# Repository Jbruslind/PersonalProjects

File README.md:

#	Personal projects

This section contains all the personal projects I'm currently working on or have worked on/finished 
(who am I kidding they're never finished). Each directory should have it's own README with details about 
what the project is and the steps I took to do it. Some of my personal favorites are: 

##	Infinity Stone Pendants 
This project was inspired by Marvel's blockbuster hits (Avengers and their derivatives) and because of a 
gift I had made previously for an old high school friend. There isn't any functional point to this, mostly
just for sentimental value.

The design revolves around the use of [Tritium](https://nuclearsafety.gc.ca/eng/pdfs/Fact_Sheets/January-2013-Fact-Sheet-Tritium_e.pdf) 
which is a radioactive isotope of hydrogen. It's not radioactive in the sense that it'll cause damage, 
just enough to create some cool glowing effects. The radiation is low levels of Beta-particles and is not
damaging unless ingested (so just don't eat the vials). Using this as a core, I created geometric designs 
corresponding to each stone and their back story/ability. 

Here's a picture of the full assembly. The metal colors are pretty off due to Inventor having weird colors...

## More information can be found [here!](https://github.com/Jbruslind/PersonalProjects/tree/master/Inventor%20Projects/Infinity)

##	Automatic Terrarium 

This project is like 3 years in the making. All it's supposed to do is control some simple LEDs and a water pump
for a generic plant in a pot. This is supposed to be like a simple arduino project, but it's taken me 3 years and
3 iterations to actually get it done. To be fair, each time I'll work on it for around a week, get distracted for 
6 months and come back to it. 

But it was a fun project to work on and I think the recent revision looks pretty cool. 

## More information can be found 

### V1 -> ~2016

### V2 -> ~2018

### V3 -> ~2019

##	UWROV19

This project is the Underwater ROV team 2018-2019 circuit board files. These circuits were specially designed so that they would fit inside a 
cylindrical pressure housing. Because of this we were able to use a standard PCB footprint for all our designs . 
All of these were either designed by me or with me as the team lead.

The basic idea was to abstract certain, similar components of an Underwater ROV onto these circuit boards and then to connect them all together 
inside a pressure housing. These components included: Brushless motor control, power supply/delivery, sensor integration (pressure, distance, angular
rotation), ground station signal delivery and actuator control. 

## More information can be found

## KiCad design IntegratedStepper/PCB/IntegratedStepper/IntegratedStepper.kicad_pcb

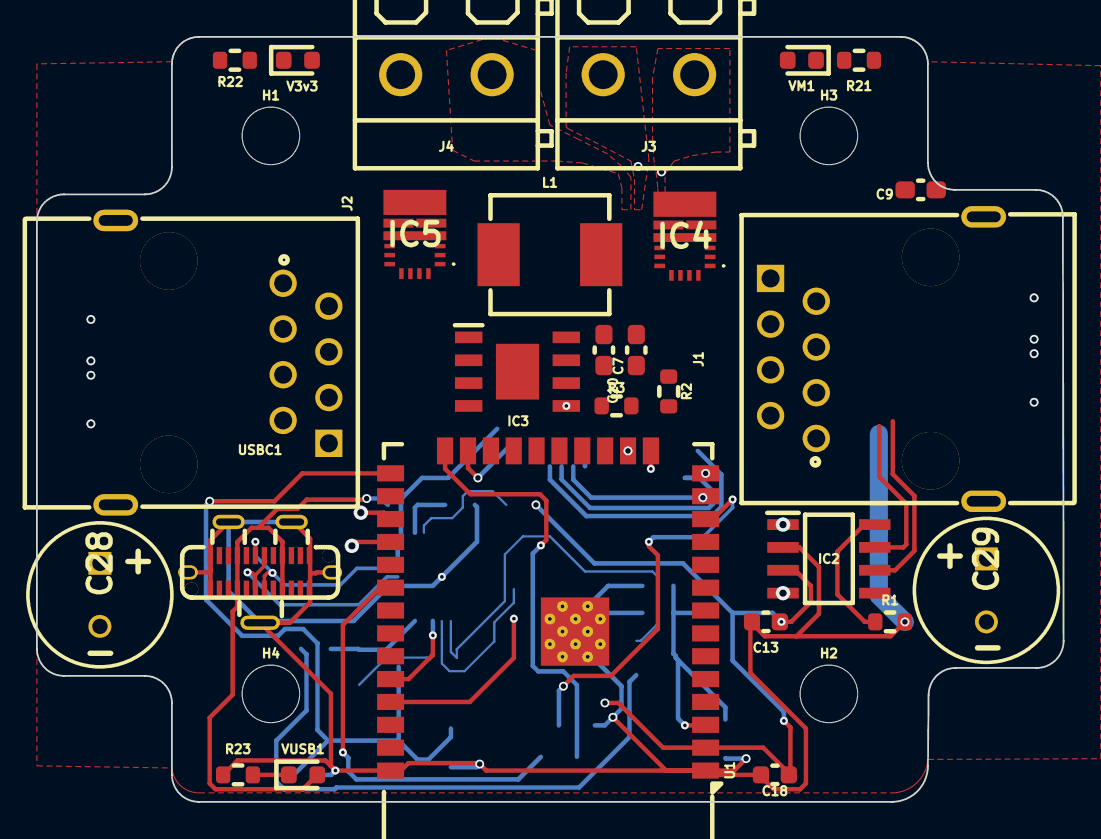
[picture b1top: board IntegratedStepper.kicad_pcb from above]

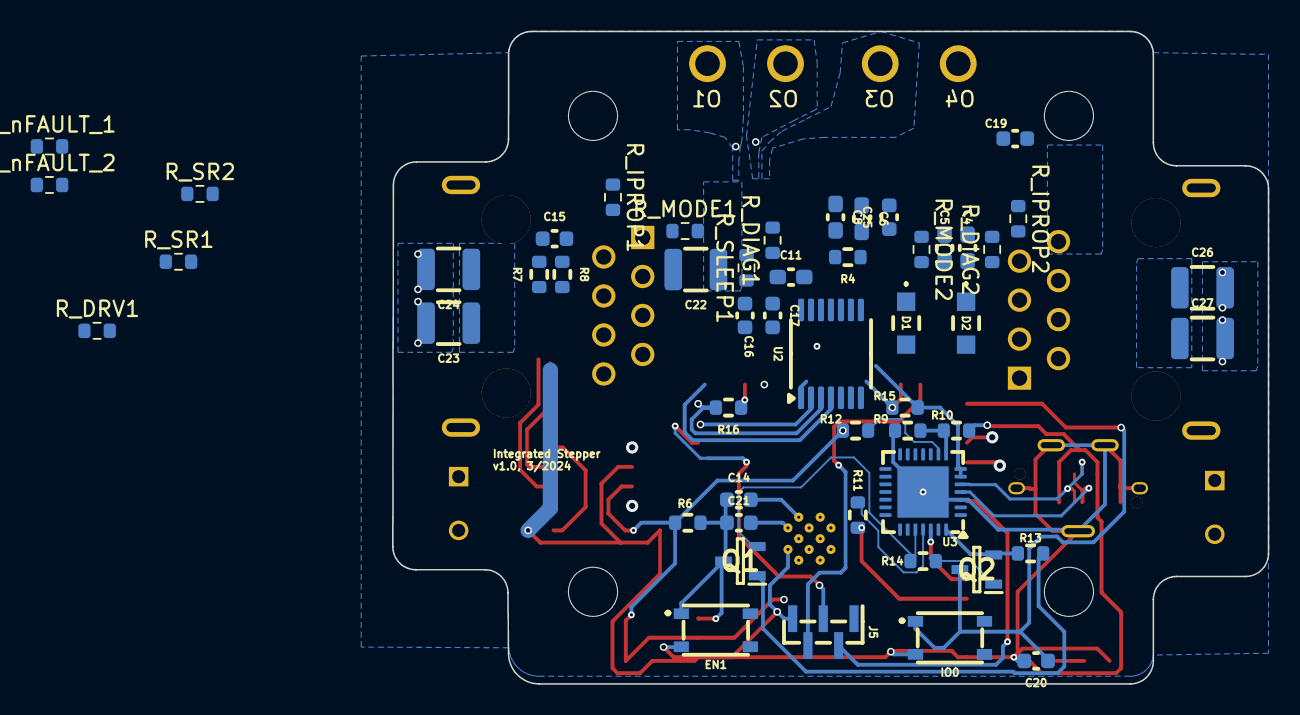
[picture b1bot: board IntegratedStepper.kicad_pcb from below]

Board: 4 copper layers, 57.0 x 42.5 mm, 82 parts (51 on the bottom side), 58 nets.

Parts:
C4, C7, C10: 10uf; C_0603_1608Metric_Pad1.08x0.95mm_HandSolder
C5, C9: 1uF; C_0603_1608Metric_Pad1.08x0.95mm_HandSolder
C6, C8: 100nf; C_0603_1608Metric_Pad1.08x0.95mm_HandSolder
C11: 0.1uF; C_0603_1608Metric_Pad1.08x0.95mm_HandSolder
C13, C14, C17, C18, C20, C21: 0.1uF; C_0603_1608Metric
C15: 4.7nF; C_0603_1608Metric
C16, C19, C25: 10uF; C_0603_1608Metric
C22, C23: 22uF; C_1210_3225Metric
C24, C26, C27: 10uF; C_1210_3225Metric
C28, C29: 100uF; CAPPRD350W65D800H1650
D1, D2: PMEG6020ER,115; PMEG6020ER115
EN1: PTS815_SJG_250_SMTR_LFS; PTS815SJM250SMTRLFS
H1, H2, H3, H4: MountingHole_Pad; MountingHole_3.2mm_M3
IC2: SN65HVD230DR; SOT127P600X175-8N
IC3: LMR38020FSQDDARQ1; SOIC127P600X170-9N
IC4, IC5: DRV8243HQRXYRQ1
IO0: PTS815_SJG_250_SMTR_LFS; PTS815SJM250SMTRLFS
J1, J2: 8P8C; RJ45-TH_KH-RJ45-58-8P8C
J3, J4: Screw_Terminal_01x02; CONN-TH_P5.08_KF128-5.08-2P
J5: Conn_01x05_Socket; PinHeader_1x05_P1.00mm_Vertical_SMD_Pin1Left
L1: 10uH; IND-SMD_L7.2-W6.6_GPSR07X0
Q1, Q2: SS8050-G; SOT95P240X115-3N
R1, R6, R13, R14: 10k; R_0603_1608Metric
R2: 154k; R_0603_1608Metric
R3, R4: 64.9k; R_0603_1608Metric
R7, R8: 60; R_0603_1608Metric
R9: 47.5k; R_0603_1608Metric
R10: 22.1k; R_0603_1608Metric
R11: 10; R_0603_1608Metric
R12, R15, R16: 2k; R_0603_1608Metric
R21: 10K; R_0603_1608Metric
R22, R23: 500; R_0603_1608Metric
R_DIAG1, R_DIAG2: 8.2k; R_0603_1608Metric
R_DRV1: 2k; R_0603_1608Metric
R_IPROP1, R_IPROP2: 820; R_0603_1608Metric
R_MODE1, R_MODE2: 8.2k; R_0603_1608Metric
R_SLEEP1: 2k; R_0603_1608Metric
R_SR1, R_SR2: 8.2k; R_0603_1608Metric
R_nFAULT_1, R_nFAULT_2: 2k; R_0603_1608Metric
U1: ESP32-WROOM-32E; ESP32-WROOM-32D
U2: AS5048A; TSSOP-14_4.4x5mm_P0.65mm
U3: CP2102N-Axx-xQFN28; QFN-28-1EP_5x5mm_P0.5mm_EP3.35x3.35mm
USBC1: TYPE-C 3.1_C168690; USB-C-SMD_TYPE-C-USB-3
V3v3: LED; LED_0603_1608Metric
VM1: LED; LED_0603_1608Metric
VUSB1: LED; LED_0603_1608Metric

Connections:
3V3_VCC: C7.1, C8.1, C9.1, C10.1, C13.1, C16.1, C17.1, C18.1, C19.1, IC2.3 (VCC), J5.1, L1.2, R2.1, R6.1, R12.2, R15.2, R_SLEEP1.1, R_nFAULT_1.2, R_nFAULT_2.2, U1.2 (VDD), U2.11 (VDD5V), U2.12 (VDD3V), U3.6 (VDD), U3.7 (VREGIN), V3v3.2 (A)
/3V3_VReg/VM: C22.1, C23.1, C24.1, C25.1, C26.1, C27.1, C28.1 (+), C29.1 (+), D1.2 (A), IC4.4 (VM), IC5.4 (VM), J1.1, J1.2, J2.1, J2.2, VM1.2 (A)
/CAN_Transciever/CAN_RX: IC2.4 (R), U1.28 (IO17)
/CAN_Transciever/CAN_TX: IC2.1 (D), U1.27 (IO16)
/DRV8844/DRVOFF: IC4.8 (DRVOFF), IC5.8 (DRVOFF), R_DRV1.2, U1.26 (IO4)
/DRV8844/IN1: IC4.9 (EN/IN1), U1.10 (IO25)
/DRV8844/IN2: IC4.10 (PH/IN2), U1.11 (IO26)
/DRV8844/IN3: IC5.9 (EN/IN1), U1.9 (IO33)
/DRV8844/IN4: IC5.10 (PH/IN2), U1.8 (IO32)
/DRV8844/NFAULT_1: IC4.1 (NFAULT), R_nFAULT_1.1, U1.31 (IO19)
/DRV8844/NFAULT_2: IC5.1 (NFAULT), R_nFAULT_2.1, U1.37 (IO23)
/DRV8844/NSLEEP: IC4.3 (NSLEEP), IC5.3 (NSLEEP), R_SLEEP1.2, U1.29 (IO5)
/DRV8844/OUT1: IC4.7 (OUT1), J3.1
/DRV8844/OUT2: IC4.5 (OUT2), J3.2
/DRV8844/OUT3: IC5.7 (OUT1), J4.1
/DRV8844/OUT4: IC5.5 (OUT2), J4.2
/ESP32_MCU/ENC+: J5.3, U1.12 (IO27)
/ESP32_MCU/ENC-: J5.2, U1.30 (IO18)
/ESP32_MCU/ENC_IND: J5.4, U1.24 (IO2)
/ESP32_MCU/M_CS0: R15.1, U1.23 (IO15), U2.1 (~CSn)
/ESP32_MCU/M_MISO: R16.2, U1.14 (IO12), U2.3 (MISO)
/ESP32_MCU/M_MOSI: U1.16 (IO13), U2.4 (MOSI)
/ESP32_MCU/M_SCLK: U1.13 (IO14), U2.2 (CLK)
CANH: IC2.6 (CANL), J1.5, J2.5, R7.1
CANL: IC2.7 (CANH), J1.4, J2.4, R8.2
DTR: Q2.2 (E), R13.1, U3.28 (~DTR)
EN: C14.1, C21.1, EN1.1 (COM_1), Q1.3 (C), R6.2, U1.3 (EN)
GND: C4.1, C5.1, C6.1, C7.2, C8.2, C9.2, C10.2, C13.2, C14.2, C15.2, C16.2, C17.2, C18.2, C19.2, C20.2, C21.2, C22.2, C23.2, C24.2, C25.2, C26.2, C27.2, C28.2 (-), C29.2 (-), EN1.3 (NO_1), IC2.2 (GND), IC3.1 (GND), IC3.9 (EP), IC4.6 (GND), IC5.6 (GND), IO0.3 (NO_1), J1.3, J1.6, J2.3, J2.6, J5.5, R1.2, R3.2, R4.2, R9.2, R16.1, R21.1, R22.1, R23.1, R_DIAG1.1, R_DIAG2.1, R_DRV1.1, R_IPROP1.2, R_IPROP2.2, R_MODE1.1, R_MODE2.1, R_SR1.1, R_SR2.1, U1.1 (GND), U1.15 (GND), U1.38 (GND), U1.39 (GND), U2.13 (GND), U3.3 (GND), U3.29 (GND), USBC1.0, USBC1.A1, USBC1.A12, USBC1.B1, USBC1.B12
IO0: C20.1, IO0.1 (COM_1), Q2.3 (C), U1.25 (IO0)
IPROPI_1: IC4.2 (IPROPI), R_IPROP1.1, U1.6 (IO34)
IPROPI_2: IC5.2 (IPROPI), R_IPROP2.1, U1.7 (IO35)
unnamed: C15.1, R7.2, R8.1
unnamed: IC2.8 (RS), R1.1
unnamed: C11.1, IC3.7 (BOOT)
unnamed: IC3.5 (FB), R2.2, R3.1
unnamed: IC3.4 (RT/SYNC), R4.1
unnamed: C11.2, IC3.8 (SW), L1.1
unnamed: IC4.11 (DIAG), R_DIAG1.2
unnamed: IC4.14 (MODE), R_MODE1.2
unnamed: IC4.12 (SR), R_SR1.2
unnamed: IC5.11 (DIAG), R_DIAG2.2
unnamed: IC5.14 (MODE), R_MODE2.2
unnamed: IC5.12 (SR), R_SR2.2
unnamed: Q1.1 (B), R13.2
unnamed: Q2.1 (B), R14.2
unnamed: R11.2, U1.35 (TXD0/IO1)
unnamed: R9.1, R10.1, U3.8 (VBUS)
unnamed: R12.1, U3.9 (~RST)
unnamed: R22.2, V3v3.1 (K)
unnamed: R21.2, VM1.1 (K)
unnamed: R23.2, VUSB1.1 (K)
RTS: Q1.2 (E), R14.1, U3.24 (~RTS)
RX: U1.34 (RXD0/IO3), U3.26 (TXD)
TX: R11.1, U3.25 (RXD)
USB_D+: U3.4 (D+), USBC1.A6, USBC1.B6
USB_D-: U3.5 (D-), USBC1.A7, USBC1.B7
VIN: C4.2, C5.2, C6.2, D1.1 (K), D2.1 (K), IC3.2 (EN), IC3.3 (VIN)
V_USB: D2.2 (A), R10.2, USBC1.A4, USBC1.A9, USBC1.B4, USBC1.B9, VUSB1.2 (A)

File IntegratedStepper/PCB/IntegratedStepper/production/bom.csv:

Designator,Footprint,Quantity,Value,LCSC Part #
"C1, C3",0805,2,0.01uF,C303894
"C10, C4, C7",0603,3,10uf,C96446
C11,0603,1,0.1uF,C14663
"C12, C16, C19, C25",0603,4,10uF,
"C13, C14, C18, C20, C21",0603,5,0.1uF,
C17,0603,1,0.1uF,C2929200
C2,0805,1,0.1uF,C597290
"C22, C23",1210,2,22uF,C2929200
"C24, C26, C27",1210,3,10uF,
"C5, C9",0603,2,1uF,C15849
"C6, C8",0603,2,100nf,C14663
"D1, D2",PMEG6020ER115,2,"PMEG6020ER,115",C98663
"EN1, IO0",PTS815SJM250SMTRLFS,2,PTS815_SJG_250_SMTR_LFS,C411883
IC1,SOP65P640X120-29N,1,DRV8844PWPR, C177807
IC2,SOT127P600X175-8N,1,SN65HVD230DR,
IC3,SOIC127P600X170-9N,1,LMR38020FSQDDARQ1,C5149193
"J1, J2",RJ45-TH_KH-RJ45-58-8P8C,2,8P8C,C2683360
"J3, J4",CONN-TH_P5.08_KF128-5.08-2P,2,Screw_Terminal_01x02,C474952
L1,IND-SMD_L7.2-W6.6_GPSR07X0,1,10uH,C5189959
"Q1, Q2",SOT95P240X115-3N,2,SS8050-G,C916392
"R1, R13, R14, R21, R6",0603,5,10k,C469659
R10,0603,1,22.1k,C2989573
R11,0603,1,10,C177687
"R12, R15, R16, R19, R20",0603,5,2k,C217936
R2,0603,1,154k,C425661
"R22, R23",0603,2,500,C2989147
"R3, R4",0603,2,64.9k, C912530
R9,0603,1,47.5k,C319608
U1,ESP32-WROOM-32D,1,ESP32-WROOM-32E,C701341
U2,TSSOP-14_4.4x5mm_P0.65mm,1,AS5048A,C2655181
U3,QFN-28-1EP_5x5mm_P0.5mm_EP3.35x3.35mm,1,CP2102N-Axx-xQFN28,C964632
USBC1,USB-C-SMD_TYPE-C-USB-3,1,TYPE-C 3.1_C168690,C168690
"V3v3, VM1, VUSB1",0603,3,LED,C965804

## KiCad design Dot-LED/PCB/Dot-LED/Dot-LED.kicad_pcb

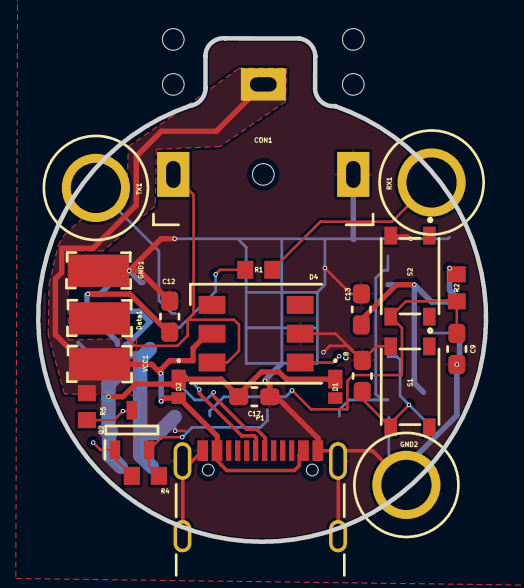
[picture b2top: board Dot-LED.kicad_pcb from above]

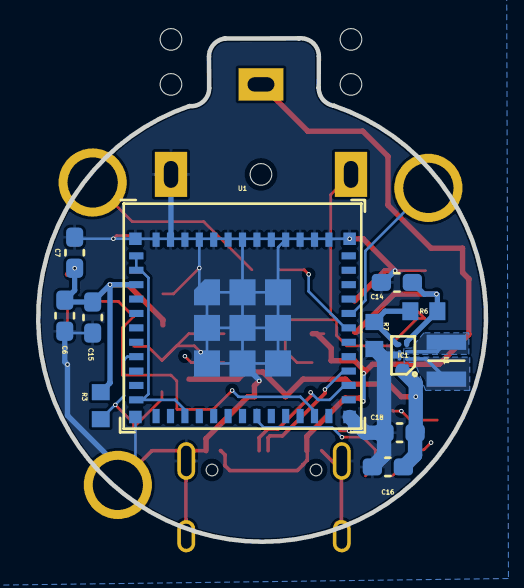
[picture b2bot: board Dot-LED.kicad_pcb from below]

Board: 4 copper layers, 24.9 x 28.0 mm, 35 parts (12 on the bottom side), 18 nets.

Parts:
C6, C12, C17: 1uF; C_0603_1608Metric_Pad1.08x0.95mm_HandSolder
C7, C8, C9, C13, C18: 100nf; C_0603_1608Metric_Pad1.08x0.95mm_HandSolder
C14, C15, C16: 10uf; C_0603_1608Metric_Pad1.08x0.95mm_HandSolder
CON1: SJ1-3523N; Headphone_Jack_3.5mm_SJ1-3523N
D1, D2: PMEG2020EPK,315; PMEG2020EPK315
D4: WS2813; LED_WS2812_PLCC6_5.0x5.0mm_P1.6mm
Data1: RCW-0C; PROBE_PAD_1206
GND1: RCW-0C; PROBE_PAD_1206
GND2: 1508-0-57-15-00-00-03-0; Test-Point-Pin_Drill2.79mm
IC1: TPS631010YBGR; BGA8C40P2X4_86X176X50
L1: DFE252012PD-1R0M=P2; DFE2HCAH1R0MJ0L
P1: USB_C_Plug; USB_C_Receptacle_GCT_USB4105-xx-A_16P_TopMnt_Horizontal
Q2: BSS138P,215; SOT95P230X110-3N
R1: 1; RESC1608X55N
R2, R3, R4, R5: 15k; RESC1608X55N
R6: 511k; RESC1608X55N
R7: 91k; RESC1608X55N
RX1: 1508-0-57-15-00-00-03-0; Test-Point-Pin_Drill2.79mm
S1, S2: PTS815_SJM_250_SMTR_LFS; PTS815SJM250SMTRLFS
TX1: 1508-0-57-15-00-00-03-0; Test-Point-Pin_Drill2.79mm
U1: ESP32-C3-MINI-1; ESP32-C3-MINI-1U
VCC1: RCW-0C; PROBE_PAD_1206

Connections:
3V3_VCC: C6.2, C7.2, C12.1, C13.1, C14.1, C15.1, IC1.D1 (VOUT), Q2.1, R2.2, R3.2, R4.2, R6.1, U1.3 (3V3)
5V: CON1.1 (S), D2.2, D4.2 (VDD), P1.A4 (VBUS), P1.A9 (VBUS), P1.B4 (VBUS), P1.B9 (VBUS), R5.2, VCC1.1
/ESP32C3_MCU/5V_DIN: D4.4 (DIN), Q2.3, R5.1
/ESP32C3_MCU/ESP_DN: P1.A7 (D-), U1.26 (GPIO18/USB_D-)
/ESP32C3_MCU/ESP_DP: P1.A6 (D+), U1.27 (GPIO19/USB_D+)
D5: Q2.2, R4.1, U1.19 (GPIO5/ADC2_CH0)
D5_out: CON1.2 (T), D4.3 (DOUT), Data1.1
D9: C9.2, R2.1, S2.4 (NO_2), U1.23 (GPIO9)
EN: C8.2, R3.1, S1.4 (NO_2), U1.8 (EN/CHIP_PU)
GND: C6.1, C7.1, C8.1, C9.1, C12.2, C13.2, C14.2, C15.2, C16.1, C17.1, C18.1, CON1.3 (R), D4.5 (GND), GND1.1, GND2.1, IC1.B2 (MODE), IC1.C2 (GND), P1.A1 (GND), P1.A12 (GND), P1.B1 (GND), P1.B12 (GND), P1.S1 (SHIELD), R7.2, S1.3 (NO_1), S2.3 (NO_1), U1.36 (GND), U1.37 (GND), U1.38 (GND), U1.39 (GND), U1.40 (GND), U1.41 (GND), U1.42 (GND), U1.43 (GND), U1.44 (GND), U1.45 (GND), U1.46 (GND), U1.47 (GND), U1.48 (GND), U1.49 (GND), U1.50 (GND), U1.51 (GND), U1.52 (GND), U1.53 (GND)
L1: IC1.B1 (LX1), L1.1
unnamed: IC1.D2 (FB), R6.2, R7.1
unnamed: IC1.C1 (LX2), L1.2
unnamed: U1.1 (GND), U1.2 (GND), U1.11 (GND), U1.14 (GND)
unnamed: R1.2, U1.30 (GPIO20/U0RXD)
RX_D7: R1.1, RX1.1
TX_D6: TX1.1, U1.31 (GPIO21/U0TXD)
VIN: C16.2, C17.2, C18.2, D1.1, D2.1, IC1.A1 (VIN), IC1.A2 (EN)

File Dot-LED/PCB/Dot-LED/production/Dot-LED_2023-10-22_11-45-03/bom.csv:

Designator,Footprint,Quantity,Value,LCSC Part #
"C12, C17, C6",0603,3,1uF,C15849
"C13, C18, C7, C8, C9",0603,5,100nf,C14663
"C14, C15, C16",0603,3,10uf,C96446
CON1,Headphone_Jack_3.5mm_SJ1-3523N,1,SJ1-3523N,
"D1, D2",PMEG2020EPK315,2,"PMEG2020EPK,315",C552841
D4,LED_WS2812_PLCC6_5.0x5.0mm_P1.6mm,1,WS2813,C114592
"Data1, GND1, VCC1",PROBE_PAD_1206,3,RCW-0C,
"GND2, RX1, TX1",Test-Point-Pin_Drill2.79mm,3,1508-0-57-15-00-00-03-0,
IC1,BGA8C40P2X4_86X176X50,1,TPS631010YBGR,C6719123
L1,DFE2HCAH1R0MJ0L,1,DFE252012PD-1R0M=P2,C285917
P1,USB-C_Female_E8124-015-01,1,USB_C_Plug,C134113
R1,RESC1608X55N,1,1,C247057
"R2, R3",RESC1608X55N,2,15k,C22809
R6,RESC1608X55N,1,511k,C3016414
R7,RESC1608X55N,1,91k,C101235
"S1, S2",PTS815SJM250SMTRLFS,2,PTS815_SJM_250_SMTR_LFS,C411883
U1,ESP32-C3-MINI-1U,1,ESP32-C3-MINI-1,C2911374

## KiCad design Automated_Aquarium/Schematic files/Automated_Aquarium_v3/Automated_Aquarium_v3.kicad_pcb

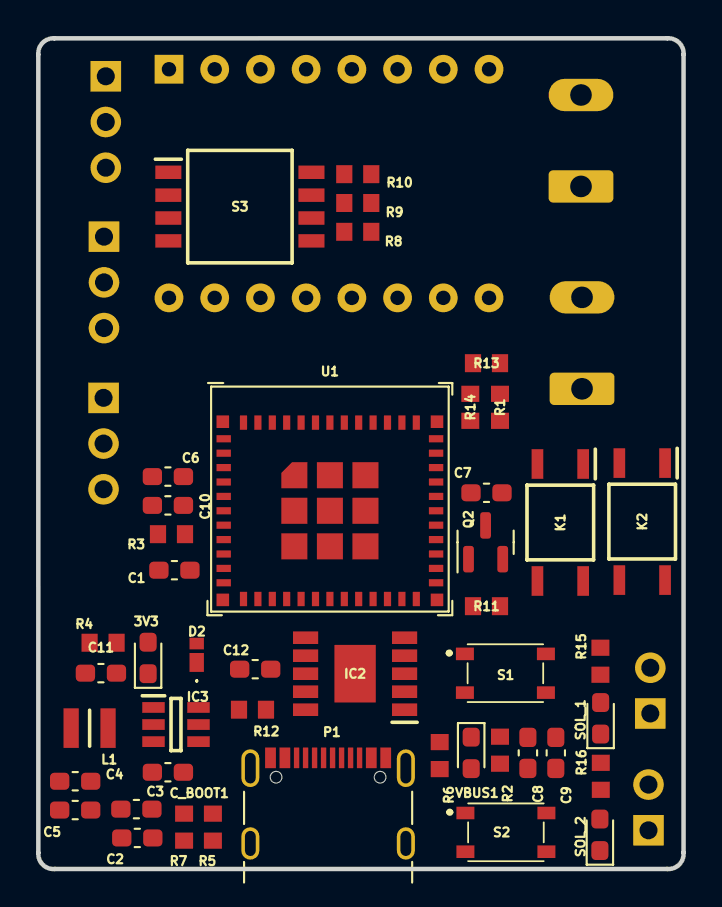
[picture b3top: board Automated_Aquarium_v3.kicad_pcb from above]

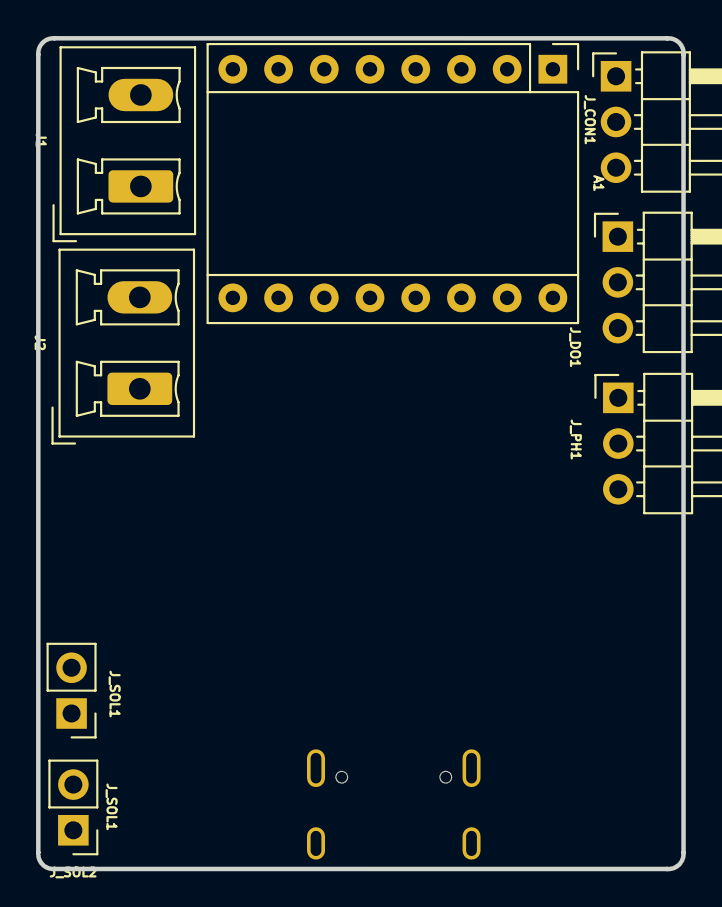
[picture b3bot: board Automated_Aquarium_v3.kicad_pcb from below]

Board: 2 copper layers, 35.9 x 46.2 mm, 53 parts (8 on the bottom side), 40 nets, no tracks yet.

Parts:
3V3: LED; LED_0603_1608Metric_Pad1.05x0.95mm_HandSolder
A1: Pololu_Breakout_A4988; Pololu_Breakout-16_15.2x20.3mm
C1, C4, C11: 10uf; C_0603_1608Metric_Pad1.08x0.95mm_HandSolder
C2, C5, C6, C12: 1uF; C_0603_1608Metric_Pad1.08x0.95mm_HandSolder
C3, C7, C8, C9, C10: 100nf; C_0603_1608Metric_Pad1.08x0.95mm_HandSolder
C_BOOT1: 100nF; C_0603_1608Metric_Pad1.08x0.95mm_HandSolder
D2: PMEG2020EPK,315; PMEG2020EPK315
IC2: CH224K; SOP100P600X180-11N
IC3: LMR51420XFDDCR; SOT95P280X110-6N
J1, J2: Screw_Terminal_01x02; PhoenixContact_MCV_1,5_2-G-5.08_1x02_P5.08mm_Vertical
J_CON1: Conn_01x03; PinHeader_1x03_P2.54mm_Horizontal
J_DO1: Conn_01x03; PinHeader_1x03_P2.54mm_Horizontal
J_PH1: Conn_01x03; PinHeader_1x03_P2.54mm_Horizontal
J_SOL1, J_SOL2: Conn_01x02; PinHeader_1x02_P2.54mm_Vertical
K1, K2: G3VM-61VY3_TR05_; SOP254P700X230-4N
L1: 8.2uH; DFE2HCAH1R0MJ0L
P1: USB_C_Plug; USB_C_Receptacle_GCT_USB4105-xx-A_16P_TopMnt_Horizontal
Q2: PMOS; SOT-23
R1: 1; RESC1608X55N
R2, R3, R6, R8, R9, R10, R11, R15, R16: 15k; RESC1608X55N
R4, R12: 1k; RESC1608X55N
R5: 100k; RESC1608X55N
R7: 22.1k; RESC1608X55N
R13, R14: 3k; RESC1608X55N
S1, S2: PTS815_SJM_250_SMTR_LFS; PTS815SJM250SMTRLFS
S3: 218-4LPSTR; SOIC127P844X265-8N
SOL_1, SOL_2: LED; LED_0603_1608Metric_Pad1.05x0.95mm_HandSolder
U1: ESP32-C3-MINI-1; ESP32-C3-MINI-1U
VBUS1: LED; LED_0603_1608Metric_Pad1.05x0.95mm_HandSolder

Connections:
3V3: A1.2 (VDD), C4.1, C5.1, C6.2, C7.2, C10.1, C11.1, J_CON1.2, J_DO1.2, J_PH1.2, L1.1, R2.2, R3.2, R4.2, R5.1, R11.2, R14.2, U1.3 (3V3)
/IOConnectors/MTR1.1A: A1.4 (1A), J2.2
/IOConnectors/MTR1.1B: A1.3 (1B), J2.1
/IOConnectors/MTR1.2A: A1.5 (2A), J1.1
/IOConnectors/MTR1.2B: A1.6 (2B), J1.2
/IOConnectors/SOL1: J_SOL1.2, K1.4 (D_2), R15.2
/IOConnectors/SOL2: J_SOL2.2, K2.4 (D_2), R16.2
CC1: IC2.6 (CC1), P1.A5 (CC)
CC2: IC2.7 (CC2), P1.B5 (VCONN)
D1: J_PH1.3, U1.13 (GPIO1/ADC1_CH1/XTAL_32K_N)
D2: J_CON1.3, U1.5 (GPIO2/ADC1_CH2)
D3: J_DO1.3, U1.6 (GPIO3/ADC1_CH3)
D5: Q2.2 (G), R13.2, U1.19 (GPIO5/ADC2_CH0)
D6: A1.16 (DIR), U1.20 (GPIO6)
D7: A1.9 (~ENABLE), U1.21 (GPIO7)
D8: A1.15 (STEP), U1.22 (GPIO8)
D9: C9.2, R2.1, S2.2 (COM_2), U1.23 (GPIO9)
DM: IC2.5 (DM), P1.A7 (D-), U1.26 (GPIO18/USB_D-)
DP: IC2.4 (DP), P1.A6 (D+), U1.27 (GPIO19/USB_D+)
EN: C8.2, R3.1, S1.2 (COM_2), U1.8 (EN/CHIP_PU)
GND: 3V3.1 (K), A1.1 (GND), A1.7 (GND), C1.1, C2.1, C3.1, C4.2, C5.2, C6.1, C7.1, C8.1, C9.1, C10.2, C11.2, C12.2, IC2.2 (CFG1), IC2.3 (CFG2), IC2.11 (GND), IC3.1 (GND), J_CON1.1, J_DO1.1, J_PH1.1, K1.2 (K), K1.3 (D_1), K2.2 (K), K2.3 (D_1), P1.A1 (GND), P1.A12 (GND), P1.B1 (GND), P1.B12 (GND), P1.S1 (SHIELD), R7.2, R8.1, R9.1, R10.1, S1.3 (NO_1), S2.3 (NO_1), SOL_1.1 (K), SOL_2.1 (K), U1.36 (GND), U1.37 (GND), U1.38 (GND), U1.39 (GND), U1.40 (GND), U1.41 (GND), U1.42 (GND), U1.43 (GND), U1.44 (GND), U1.45 (GND), U1.46 (GND), U1.47 (GND), U1.48 (GND), U1.49 (GND), U1.50 (GND), U1.51 (GND), U1.52 (GND), U1.53 (GND), VBUS1.1 (K)
unnamed: 3V3.2 (A), R4.1
unnamed: A1.10 (MS1), R10.2, S3.8
unnamed: A1.11 (MS2), R9.2, S3.7
unnamed: A1.12 (MS3), R8.2, S3.6
unnamed: C_BOOT1.1, IC3.6 (CB)
unnamed: IC3.4 (FB), R5.2, R7.1
unnamed: K1.1 (A), R13.1
unnamed: K2.1 (A), Q2.1 (D)
unnamed: Q2.3 (S), R14.1
unnamed: R11.1, S3.1, S3.2, S3.3, S3.4
unnamed: R15.1, SOL_1.2 (A)
unnamed: R16.1, SOL_2.2 (A)
unnamed: U1.1 (GND), U1.2 (GND), U1.11 (GND), U1.14 (GND)
unnamed: R1.2, U1.30 (GPIO20/U0RXD)
unnamed: R6.1, VBUS1.2 (A)
SW: C_BOOT1.2, IC3.2 (SW), L1.2
VDD: IC2.1 (VDD), IC2.9 (CFG3), R12.1
VIN: C1.2, C2.2, C3.2, D2.1, IC3.3 (VIN), IC3.5 (EN)
VUSB: A1.8 (VMOT), C12.1, D2.2, IC2.8 (VBUS), J_SOL1.1, J_SOL2.1, P1.A4 (VBUS), P1.A9 (VBUS), P1.B4 (VBUS), P1.B9 (VBUS), R6.2, R12.2

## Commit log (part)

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2018-09-10 Finished power supply
2018-09-12 Added PCB files
2018-09-15 added BOMs
2018-09-24 Small updated projects
2018-09-26 Code changes
2018-09-27 Code updates
2018-12-28 Finished Aux Board
    Final design check. Upload Gerber and BOM
2018-12-29 Finished Aux board (fo realz)
    Last commit didn't have updated files. Oops
2018-12-29 More files
    Added final design files for PDB, Power Distribution, and AUX
2019-01-03 Added Altium project files
2019-01-03 Gerber files
2019-03-06 Add LM5085 Design
2019-03-23 Added Fan mount
2019-04-08 Started V3
2019-04-10 Added bot case
2019-04-10 Started carving bot case
    Started initial holes in Bot case
2019-04-27 Updated Terrarium 3D files
2019-05-04 Added Space and Time designs
2019-05-08 Added Power stone
    Started working on Power stone
2019-05-11 Finally finished orb
    Added power stone and made time stone more like movies
2019-05-13 Add modifications to infinity
2019-05-16 Added Mind
    Made mind stone based off vision's head holder thing.
2019-05-18 Added Reality pendant
    Made reality pendant based on a design found online (will post credit in .wd)
2019-05-20 Added Bevel clock
    Started Bevel Clock project. Also added infinity holder as one big stl
2019-05-24 Added spur gear
2019-05-28 Changed Soul
    Made soul holder into a more representative shape (hood + heart)
2019-05-28 Nothing Major
2019-06-01 Change Bevel gear ratio
2019-06-03 Changed file names
2019-06-04 Made Voronoi top for terrarium
    Made voronoi pattern in top part of the automatic terrarium project. Used Fusion 360 and a generator script found online
2019-06-04 Added gcode for Top terrarium
2019-06-11 finished infinity
2019-06-12 Added Music
    Music for personal use. Viola mostly
2019-06-12 Lock files from inventor
    Don't really do anything to the project, just lock files :/
2019-06-12 Add more music
2019-06-12 Made PDF of Kuchler op11
2019-06-13 Changed Orientation of models
    Added segmented models for custom printing by Shapeways. There's some special requirements so I tried to assemble them to conform with that.
2019-06-13 Modify iam
2019-06-13 Small adjustments to files
2019-06-14 Add new Kuchler op11
    Previous version was corrupted :/
2019-06-16 Add STEM camp files
    STEM camp arudino code for a demo hosted by the OSU Robotics Club for a summer camp group
2019-06-16 Add personal readme
2019-06-20 Add Circuit board
    And updated assembly + pic
2019-06-29 Change Terrarium Code
    Made terrarium code for new PCB.
2019-07-01 Start Delta arm assembly
2019-08-11 Readme updates
    Added Readme
2019-08-11 Update README.md
    Changed readme pics to right references
2019-08-20 Added Fruit piano project files
2019-08-25 Added new cards
2019-08-27 Add camera assembly
2019-08-30 Start Custom delta for fun
2019-09-01 New changes
2019-09-02 Made good top overlay for business cards
2019-09-06 Add code for fruit piano
2019-09-08 Add business card gerbers
2019-09-24 Add test stewart platform
2019-09-27 Update assembly
    Made ball joints have actual ball joint representations in Inventor. Looks ugly, but more repsonsive to actual movement
2019-09-29 Finish RPI stellar arms
2019-10-01 Remove lockfiles
2019-10-06 Change stellar photo
    Added hole to servo arm. Added bolt/nut holes to main hex assembly
2019-10-14 minor changes
2019-10-15 Add underwater motor
2019-10-15 Add better hex top
2019-11-12 Begin Project
2019-11-12 Add motor stl
2019-11-13 Change Petal, add assembly
2019-11-16 update petals
2019-11-17 Update gift
2019-11-20 update template
2019-11-23 Update tree
2019-11-30 Update Lotus
2019-12-05 Move stuff, add descriptions
2019-12-20 update petal
2019-12-30 add parts
2020-01-10 added backup gcode
2020-01-25 Add manufacturing files
2020-01-26 add pcb
2020-01-27 add spacer for lockbox
2020-01-27 Create UROV1920_Sensor.step~HEAD
2020-02-03 add pcbs
2020-02-12 add gerbers for valentines
2020-02-21 update gerber files
2020-03-04 add business cards
2020-03-16 add parts and code
2020-03-25 add card1
2020-03-28 add robot controller stuff
2020-03-29 update inventor
2020-04-07 update stewart
2020-04-07 update music
2020-04-13 update cod
2020-04-13 add change
2020-04-13 change
2020-04-13 readme
2020-04-15 add update
2020-05-10 update model
2020-05-14 update D20
2020-06-01 add better files and code
2020-06-16 add neopixel driver
2020-06-27 add assemblies
2020-07-25 add painting
2020-12-12 Bump ini from 1.3.5 to 1.3.8 in /Altium_Circuitmaker Projects/UROV1819
    Bumps [ini](https://github.com/isaacs/ini) from 1.3.5 to 1.3.8.
    - [Release notes](https://github.com/isaacs/ini/releases)
    - [Commits](https://github.com/isaacs/ini/compare/v1.3.5...v1.3.8)
2020-12-24 add spyder robot
2020-12-31 add spyder
2021-01-03 add music
2021-01-03 Bump bl from 1.2.2 to 1.2.3 in /Altium_Circuitmaker Projects/UROV1819
    Bumps [bl](https://github.com/rvagg/bl) from 1.2.2 to 1.2.3.
    - [Release notes](https://github.com/rvagg/bl/releases)
    - [Commits](https://github.com/rvagg/bl/compare/v1.2.2...v1.2.3)
2021-01-06 update lineguide
2021-01-11 update ino code
2021-01-17 inventor changes
2021-01-22 add 8020 sets
2021-02-03 changes to hyperrail
2021-02-08 update hyperrail
2021-02-08 add bottom stand
2021-02-14 add hyperrail updates
2021-02-18 add new hyperrail parts
2021-02-21 updated checkoffs
2021-02-27 add inventor files
2021-02-27 add better back bracket
2021-03-02 update rail
2021-03-05 update ivnentor
2021-03-07 uipdate dnd
2021-03-11 add pics
2021-03-15 update hyperrail pcb
2021-03-18 update grbl32
2021-03-24 update PCB
2021-03-30 add more stl files
2021-03-30 add Grbl32
2021-03-30 Bump yargs-parser in /HyperRail/Code/Grbl_Esp32/embedded
    Bumps [yargs-parser](https://github.com/yargs/yargs-parser) from 5.0.0 to 5.0.1.
    - [Release notes](https://github.com/yargs/yargs-parser/releases)
    - [Changelog](https://github.com/yargs/yargs-parser/blob/v5.0.1/CHANGELOG.md)
    - [Commits](https://github.com/yargs/yargs-parser/compare/v5.0.0...v5.0.1)
2021-04-01 add corrected PCB files
2021-04-02 Update NEMA23 shroud
2021-04-06 add spacers
2021-04-13 update PCBs to be better
2021-05-01 add hyperrail
2021-05-06 updated stands
2021-05-09 Revert "Merge branch 'master' of https://github.com/Jbruslind/PersonalProjects"
    This reverts commit 1937d495326af77b1b0356b881bd482b5a2cda9a, reversing
    changes made to b6119261e8cb8f3e6d7400024ea7c73a78d5e462.
2021-05-10 modify assembly
2021-05-11 Bump hosted-git-info in /HyperRail/Code/Grbl_Esp32/embedded
    Bumps [hosted-git-info](https://github.com/npm/hosted-git-info) from 2.8.4 to 2.8.9.
    - [Release notes](https://github.com/npm/hosted-git-info/releases)
    - [Changelog](https://github.com/npm/hosted-git-info/blob/v2.8.9/CHANGELOG.md)
    - [Commits](https://github.com/npm/hosted-git-info/compare/v2.8.4...v2.8.9)
2021-05-18 add foot
2021-05-21 add bracket
2021-06-05 add ppt and gusset
2021-06-16 add more files
2021-06-17 update models
2021-06-21 add cura profiles
2021-06-22 add foot stl
2021-06-25 add holders
2021-06-26 add stl
2021-07-03 add updates
2021-07-06 add spacer updates
2021-07-07 add carriagev2
2021-07-12 update new carriage models with 2040 cross bar
2021-07-16 edit model files for UROV
2021-07-21 update belt restraints and gussets
2021-07-31 add short x carriage version
2021-08-03 add step files for assembly
2021-08-10 add revision for mech v2
2021-08-10 add updated infinite belt version (V3)
2021-08-12 update to v3.0 x carriage
2021-08-13 Bump path-parse in /HyperRail/Code/Grbl_Esp32/embedded
    Bumps [path-parse](https://github.com/jbgutierrez/path-parse) from 1.0.6 to 1.0.7.
    - [Release notes](https://github.com/jbgutierrez/path-parse/releases)
    - [Commits](https://github.com/jbgutierrez/path-parse/commits/v1.0.7)
    ---
    updated-dependencies:
    - dependency-name: path-parse
2021-08-22 add belt holder
2021-08-25 updated models for rov
2021-08-26 update cable guide holder
2021-09-02 update requirements and models
2021-09-13 add skate wheels
2021-09-13 update assembly with bearings
2021-09-17 update y-axis carriage
2021-09-17 stashed changes
2021-09-23 update assembly with better spacings
2021-09-27 add buffer assembly
2021-10-05 update assembly with longer parts
2021-10-08 update assembly files with buffer + nema17 shroud
2021-10-08 add human model
2021-10-09 add jetson model and ebox mounting plate
2021-10-11 add standoff stl files
2021-10-19 update foot assembly
2021-10-19 add ipt and stl of standoffs
2021-10-25 modify assembly slightly
2021-10-26 add assembly files
2021-10-27 update to short assembly
2021-10-27 update full assembly with better y-axis
2021-11-01 add nema ipt
2021-11-02 add lock files
2021-11-02 add holder and updated ipt
2021-11-03 add iam files
2021-11-03 update y-assembly
2021-11-05 add stls and updated assemblies
2021-11-08 add yaxis shroud
2021-11-09 update assembly with larger shroud
2021-11-17 new presentation
2021-11-23 update bearing and bearing adapters
2021-11-24 add pulley spacer and update assembly
2021-11-29 update main assembly
2021-12-01 add bearing and sleeve
2021-12-02 update bearing to actual dimensions
2021-12-03 Revert "remove lock files"
    This reverts commit 57f7d95667a7c9d8139f0f3ec927c960751d0e52.
2021-12-06 update flanged adapter
2021-12-09 add acuator
2021-12-10 update ebox assembly
2021-12-12 remove l,ocks
2021-12-13 add universal gcode sender
2021-12-29 add cable clamp
2022-01-01 add useful model files
2022-01-04 add buffer L
2022-01-04 change full rail assembly
2022-01-05 remove lockfile from git
2022-01-05 add dell charger models
2022-01-13 update firmware and add ebox modules/updates
2022-01-14 update mag holders
2022-01-18 update ebox assembly and bottom mounts
2022-01-20 add updated spacers and assembly
2022-01-25 final update for personal repo
2022-02-17 add wk7 presentation
2022-03-01 update config
2022-03-04 update defense
2022-03-04 add test gcode over area
2022-03-05 add pdf of diagrams
2022-06-27 Bump copy-props in /HyperRail/Code/Grbl_Esp32/embedded
    Bumps [copy-props](https://github.com/gulpjs/copy-props) from 2.0.4 to 2.0.5.
    - [Release notes](https://github.com/gulpjs/copy-props/releases)
    - [Changelog](https://github.com/gulpjs/copy-props/blob/master/CHANGELOG.md)
    - [Commits](https://github.com/gulpjs/copy-props/compare/2.0.4...2.0.5)
    ---
    updated-dependencies:
2022-09-16 add pcb files
2022-09-17 add automated PCB files
2023-03-05 Add Dot-LED
    Add KiCad project. Init first few schematics
2023-03-06 update task and DND
2023-04-09 update TCP webserver
2023-05-13 add mongoose test code
2023-05-27 update character sheets
2023-08-06 add Dot LED KiCad
2023-08-06 Start inital dotLED KiCad design
2023-08-20 update diagram
2023-09-03 update DotLED Sch
2023-09-10 update templates
2023-09-15 Update DotLED Schem
2023-09-16 update DotLED
2023-09-17 Init layout for DotLED
2023-10-08 Update Vreg to in-stock component
2023-10-08 small change to schem for new vreg
2023-10-08 more small changes
2023-11-19 finalize design based on in-stock parts
    Gerber out 1.0
2023-12-10 complete 0v1 layout aquarium
2023-12-17 finish aqua schem, add inital layout
2023-12-17 minor update
2024-01-18 added code for inital wled stuff
2024-03-17 Update Dot-LED Mech files
2024-03-17 Add IntegratedStepper Project. Start dev work for PCB
2024-03-20 update Vreg for Integrated Stepper
2024-03-30 Update Integrated Stepper PCB with ESP sch and CAN sch
2024-03-31 Update Integrated Stepper with inital PCB
    This is going to be so hard :(
2024-03-31 Add intermediate layout + routing to integrated stepper
2024-03-31 remove lock files...
2024-03-31 add changes for instock parts
2024-03-31 update with more in stock parts
2024-04-01 add silkscreen text
2024-04-02 add 3D model
2024-04-02 change vias to be larger for cheaper manufacturing
2024-04-05 Add initial FW based on live testing
2024-04-19 Move Integrated Stepper to seperate repo
2024-05-05 add new components
2024-06-08 add new libraries
2024-06-10 add new symbols
